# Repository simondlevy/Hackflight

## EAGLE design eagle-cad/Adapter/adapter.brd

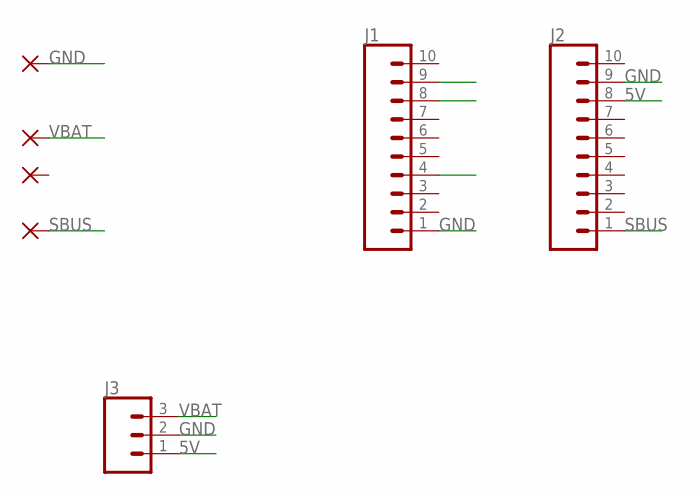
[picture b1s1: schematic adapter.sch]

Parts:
GND: SMD2; SMD1,27-2,54
J1, J2: CONN_10NO_SILK_PTH_FEMALE; 1X10_NO_SILK
J3: CONN_031X03_NO_SILK; 1X03_NO_SILK
PAD1: SMD2; SMD1,27-2,54
SBUS: SMD2; SMD1,27-2,54
VBAT: SMD2; SMD1,27-2,54

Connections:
3V3: J1.4
5V: J2.8, J3.1
GND: GND.1, J1.1, J2.9, J3.2
M2: J1.9
M3: J1.8
SBUS: J2.1, SBUS.1
VBAT: J3.3, VBAT.1

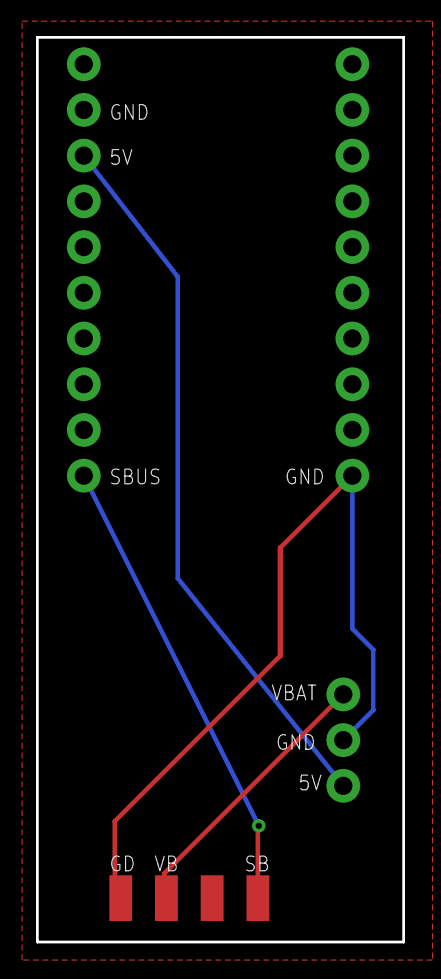
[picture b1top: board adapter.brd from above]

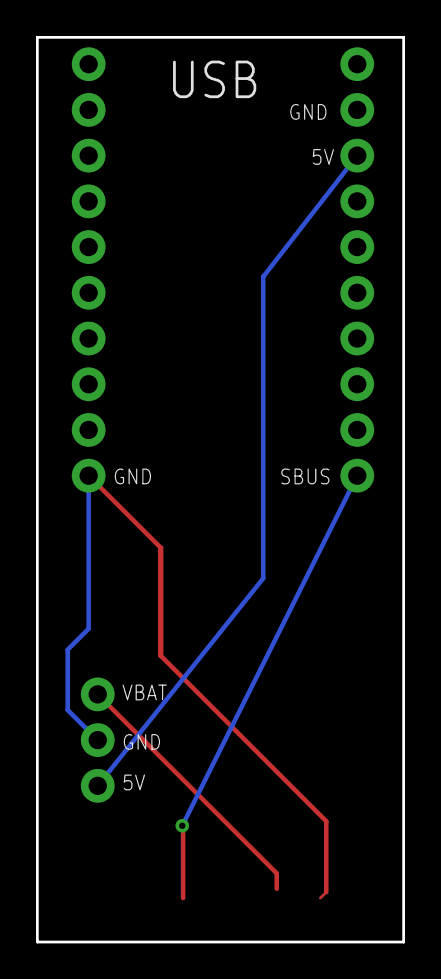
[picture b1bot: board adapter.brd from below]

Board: 2 copper layers, 20.4 x 50.3 mm, 7 parts (2 on the bottom side), 4 nets.

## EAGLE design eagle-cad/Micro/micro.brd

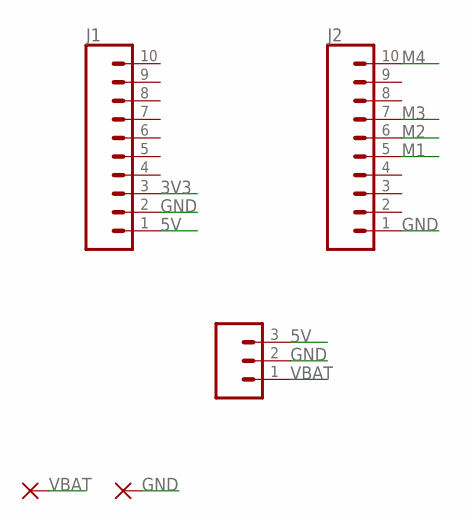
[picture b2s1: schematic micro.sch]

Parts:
J1, J2: CONN_10NO_SILK_PTH_FEMALE; 1X10_NO_SILK
J3: CONN_031X03_NO_SILK; 1X03_NO_SILK
PAD1, PAD2: SMD5; SMD2,54-5,08

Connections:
3V3: J1.3
5V: J1.1, J3.3
GND: J1.2, J2.1, J3.2, PAD2.1
M1: J2.5
M2: J2.6
M3: J2.7
M4: J2.10
VBAT: J3.1, PAD1.1

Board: 2 copper layers, 5 parts (0 on the bottom side), 3 nets, no tracks yet.

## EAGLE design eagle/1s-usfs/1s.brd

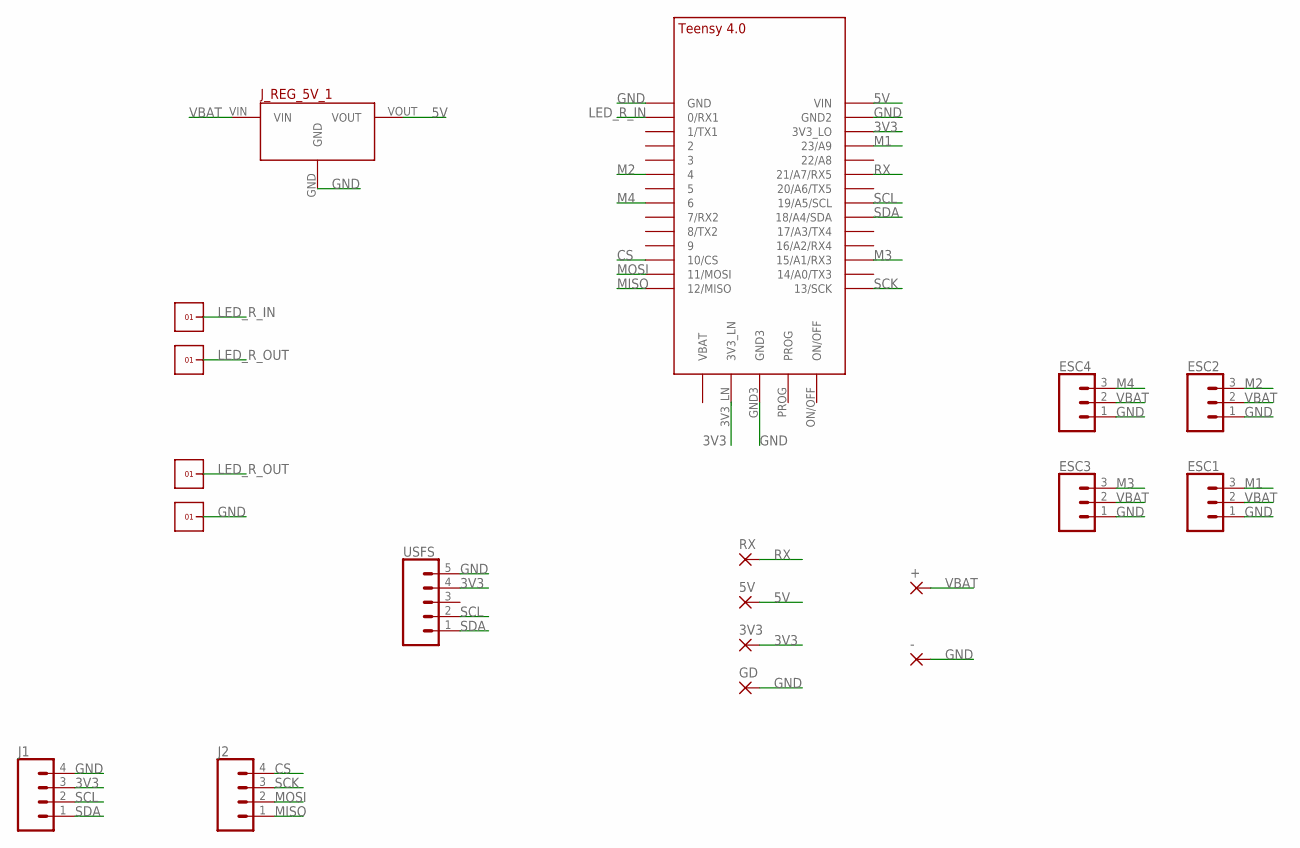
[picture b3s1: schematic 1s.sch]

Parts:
3V3, 5V: SMD2; SMD1,27-2,54
+: SMD5; SMD2,54-5,08
-: SMD5; SMD2,54-5,08
ESC1, ESC2, ESC3, ESC4: 455-1750-1-ND; 1X03
GD: SMD2; SMD1,27-2,54
J1, J2: CONN_041X04_NO_SILK; 1X04_NO_SILK
J_REG_5V_1: 5V_VOLTAGE_REGULATOR
RX: SMD2; SMD1,27-2,54
U$1: TEENSY_4.0
U$3, U$4, U$6, U$7: 1X1
USFS: CONN_05NO_SILK; 1X05_NO_SILK

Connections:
3V3: 3V3.1, J1.3, U$1.3V3_LN, U$1.3V3_LO, USFS.4
5V: 5V.1, J_REG_5V_1.VOUT, U$1.VIN
CS: J2.4, U$1.10/CS
GND: -.1, ESC1.1, ESC2.1, ESC3.1, ESC4.1, GD.1, J1.4, J_REG_5V_1.GND, U$1.GND, U$1.GND2, U$1.GND3, U$7.1, USFS.5
LED_R_IN: U$1.0/RX (0/RX1), U$3.1
LED_R_OUT: U$4.1, U$6.1
M1: ESC1.3, U$1.23/A9
M2: ESC2.3, U$1.4/CANRX (4)
M3: ESC3.3, U$1.15/A1 (15/A1/RX3)
M4: ESC4.3, U$1.6
MISO: J2.1, U$1.12/MISO
MOSI: J2.2, U$1.11/MOSI
RX: RX.1, U$1.21/A7 (21/A7/RX5)
SCK: J2.3, U$1.13/SCK
SCL: J1.2, U$1.19/A5/SCL, USFS.2
SDA: J1.1, U$1.18/A4/SDA, USFS.1
VBAT: +.1, ESC1.2, ESC2.2, ESC3.2, ESC4.2, J_REG_5V_1.VIN

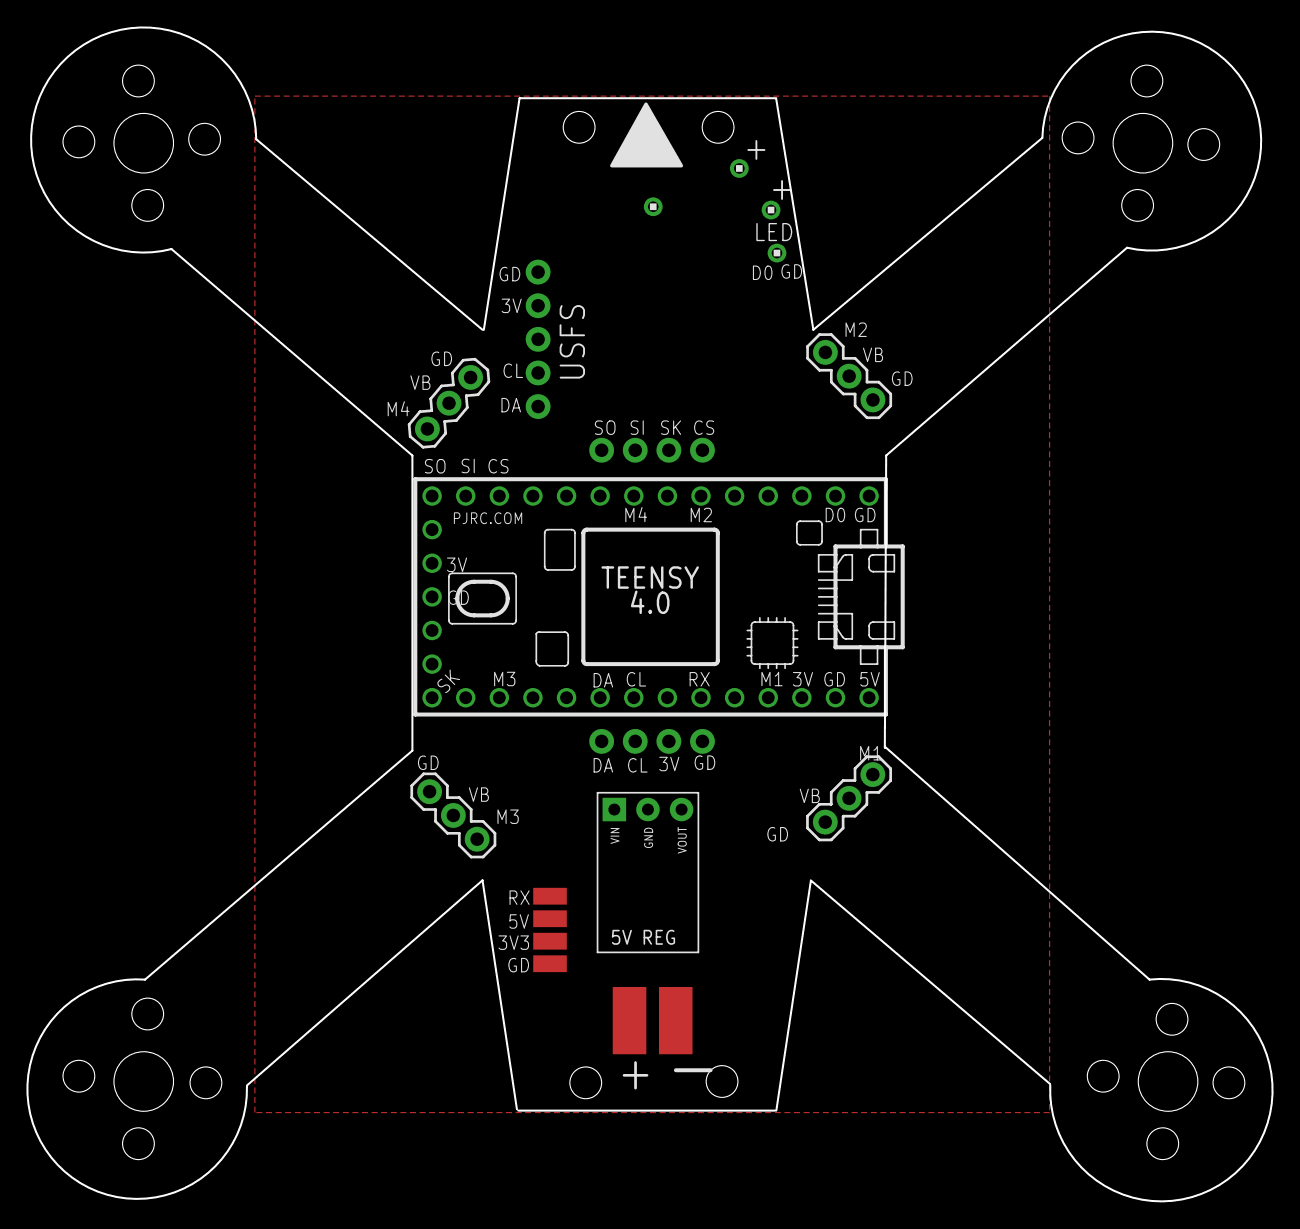
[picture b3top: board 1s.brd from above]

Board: 2 copper layers, 94.1 x 88.7 mm, 19 parts (0 on the bottom side), 17 nets.

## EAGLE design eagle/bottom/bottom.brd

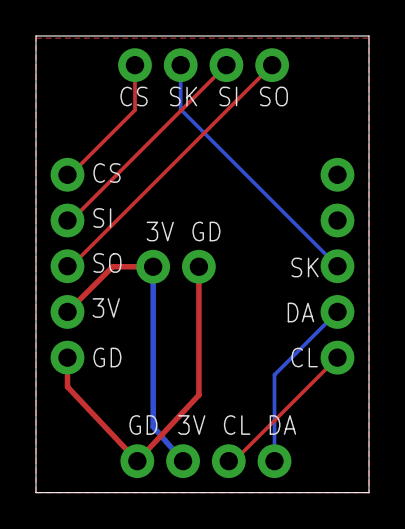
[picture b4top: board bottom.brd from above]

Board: 2 copper layers, 18.5 x 25.4 mm, 5 parts (0 on the bottom side), 8 nets.

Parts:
J3, J5: 1X04_NO_SILK
J4: 1X02_NO_SILK
J6, J7: 1X05_NO_SILK

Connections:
3V3: J3.3, J4.2, J6.2
CS: J5.1, J6.5
GND: J3.4, J4.1, J6.1
MISO: J5.4, J6.3
MOSI: J5.3, J6.4
SCK: J5.2, J7.3
SCL: J3.2, J7.1
SDA: J3.1, J7.2

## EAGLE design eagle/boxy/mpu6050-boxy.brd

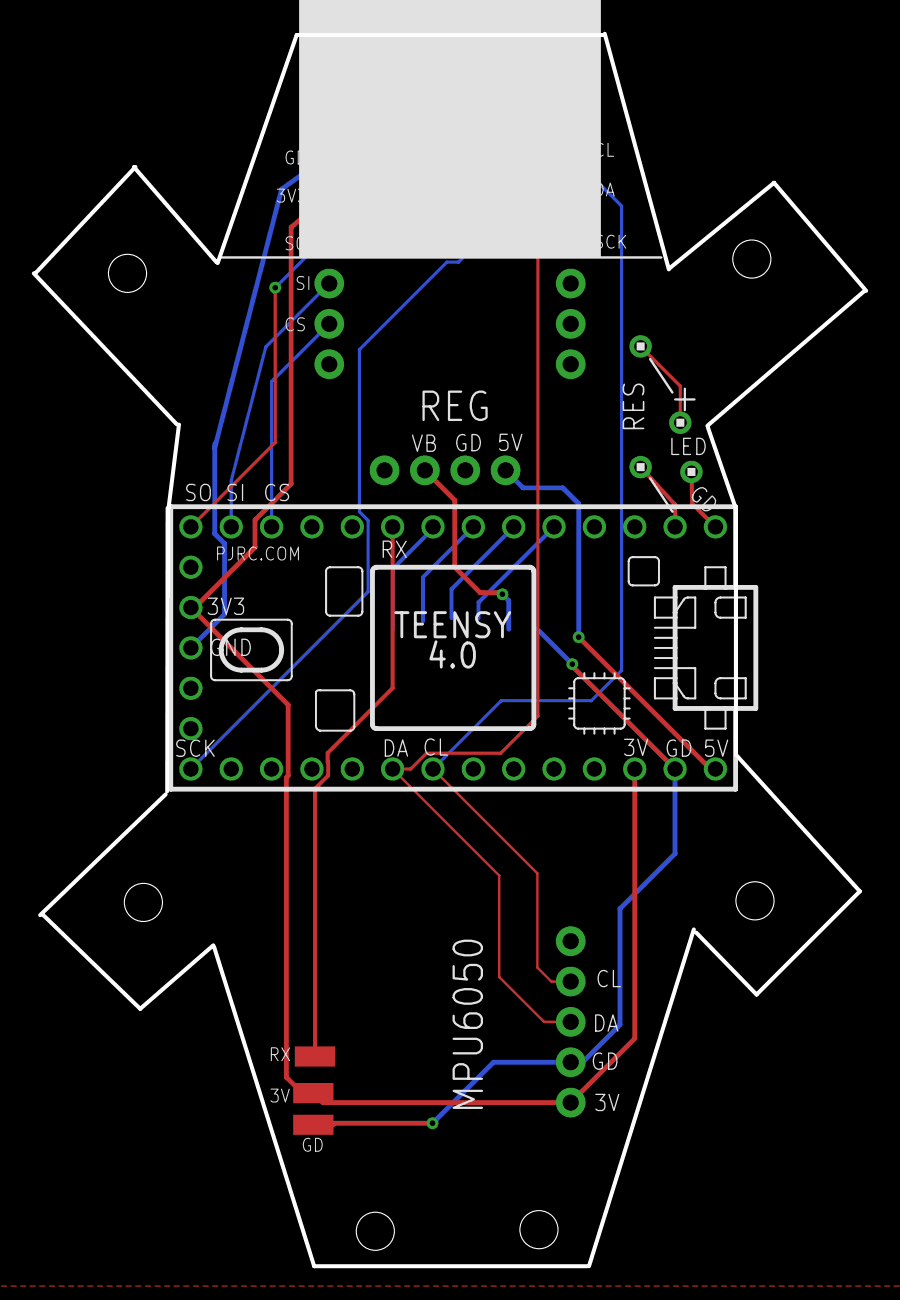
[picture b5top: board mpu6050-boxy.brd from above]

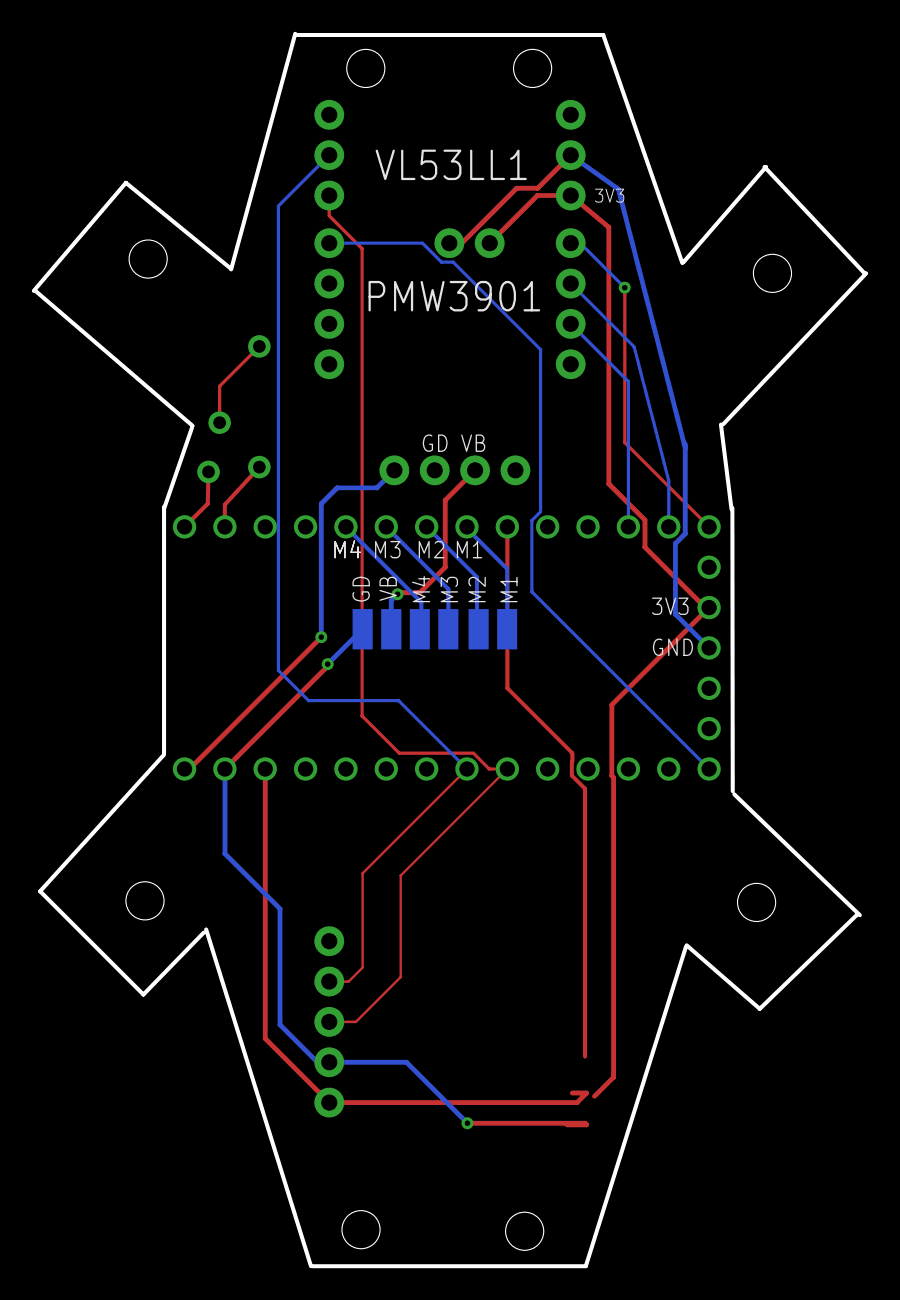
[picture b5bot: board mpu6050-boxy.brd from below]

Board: 2 copper layers, 52.4 x 77.6 mm, 21 parts (6 on the bottom side), 18 nets.

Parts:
3V: SMD1,27-2,54
GD: SMD1,27-2,54
GND: SMD1,27-2,54
J1: 1X05_NO_SILK
M1, M2, M3, M4: SMD1,27-2,54
PMW1, PMW2: 1X04_NO_SILK
PMW3: 1X02_NO_SILK
REG: 1X04_NO_SILK
RX: SMD1,27-2,54
U$1: TEENSY_4.0
U$3, U$4, U$6, U$7: 1X1
VBAT: SMD1,27-2,54
VL1, VL2: 1X03_NO_SILK

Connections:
3V3: 3V.1, J1.1, PMW3.1, U$1.3V3_LN, U$1.3V3_LO, VL2.1
5V: REG.1, U$1.VIN
CS: PMW2.3, U$1.10/CS
G2: U$1.GND, U$7.1
GND: GD.1, GND.1, J1.2, PMW3.2, REG.2, U$1.GND2, U$1.GND3, VL2.2
LED_R_IN: U$1.0/RX, U$3.1
LED_R_OUT: U$4.1, U$6.1
M1: M1.1, U$1.6
M2: M2.1, U$1.5
M3: M3.1, U$1.4/CANRX
M4: M4.1, U$1.3/CANTX
MISO: PMW2.1, U$1.12/MISO
MOSI: PMW2.2, U$1.11/MOSI
RX: RX.1, U$1.7
SCK: PMW1.1, U$1.13/SCK
SCL: J1.4, U$1.19/A5/SCL, VL1.2
SDA: J1.3, U$1.18/A4/SDA, VL1.1
VBAT: REG.3, VBAT.1

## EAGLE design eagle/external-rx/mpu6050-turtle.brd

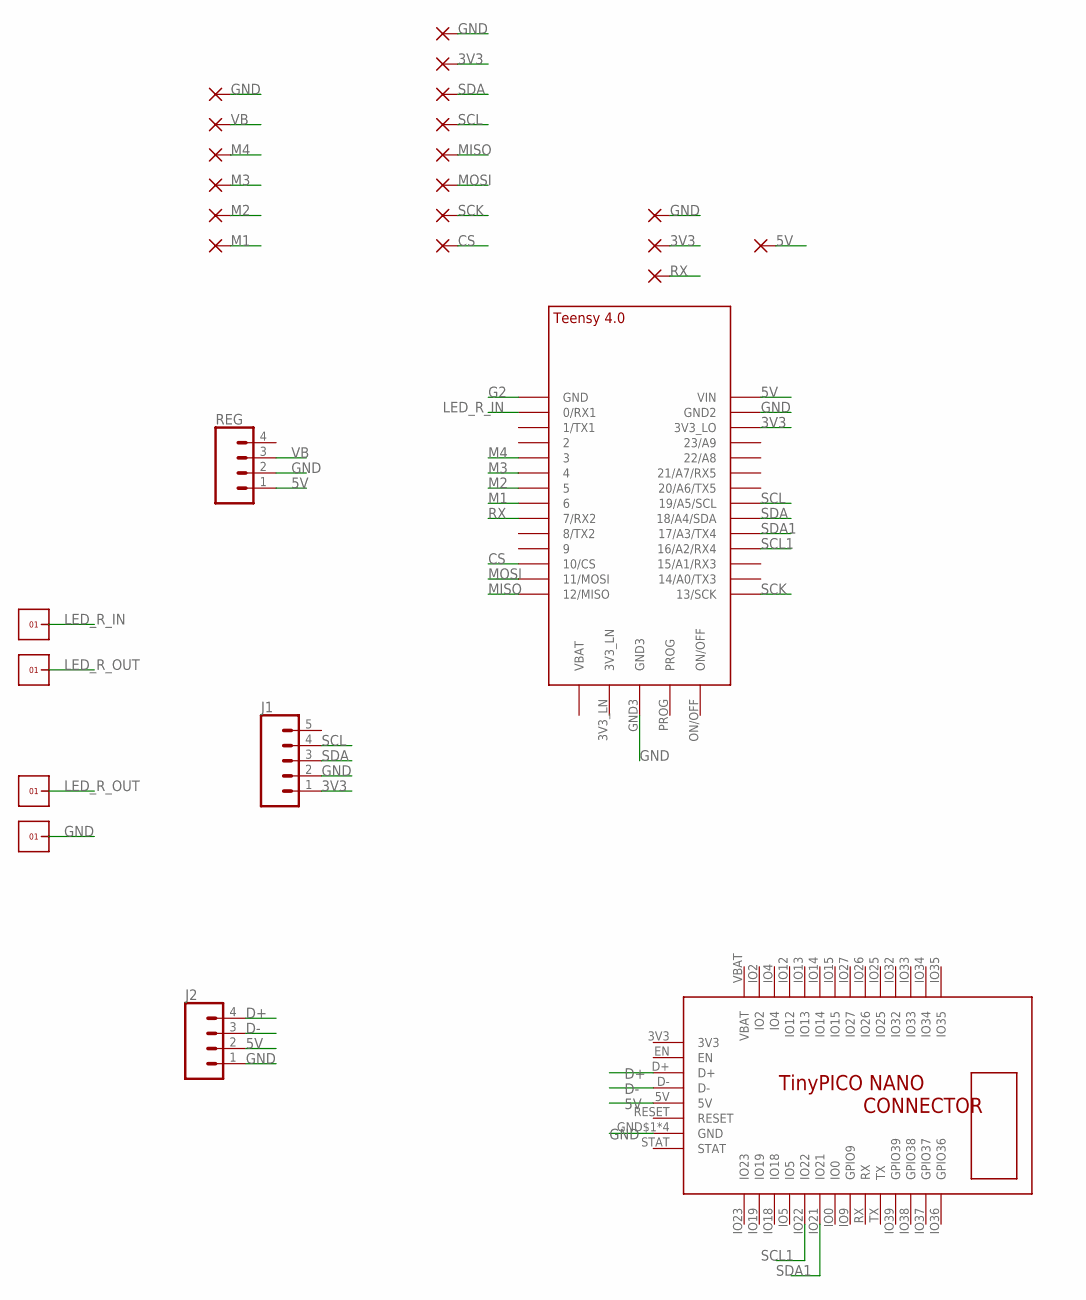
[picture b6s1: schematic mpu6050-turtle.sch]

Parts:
3V, 3V1, 3V2, 3V3: SMD2; SMD1,27-2,54
CS: SMD2; SMD1,27-2,54
GD, GD1, GD2: SMD2; SMD1,27-2,54
GND: SMD2; SMD1,27-2,54
J1: CONN_05NO_SILK; 1X05_NO_SILK
J2: CONN_041X04_NO_SILK; 1X04_NO_SILK
M1, M2, M3, M4: SMD2; SMD1,27-2,54
REG: CONN_041X04_NO_SILK; 1X04_NO_SILK
RX, RX1, RX2: SMD2; SMD1,27-2,54
SCK: SMD2; SMD1,27-2,54
U$1: TEENSY_4.0
U$2: TINYPICO-NANO-CONNECTOR
U$3, U$4, U$6, U$7: 1X1
VBAT: SMD2; SMD1,27-2,54

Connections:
3V3: 3V.1, 3V2.1, J1.1, U$1.3V3_LO, U$2.3V3
5V: 3V1.1, J2.2, REG.1, U$1.VIN, U$2.5V
CS: CS.1, U$1.10/CS
D+: J2.4, U$2.D+
D-: J2.3, U$2.D-
G2: U$1.GND
GND: GD.1, GD1.1, GND.1, J1.2, J2.1, REG.2, U$1.GND2, U$1.GND3, U$2.GND$1 (GND), U$2.GND$2 (GND), U$2.GND$3 (GND), U$2.GND$4 (GND), U$7.1
LED_R_IN: U$1.0/RX (0/RX1), U$3.1
LED_R_OUT: U$4.1, U$6.1
M1: M1.1, U$1.6
M2: M2.1, U$1.5
M3: M3.1, U$1.4/CANRX (4)
M4: M4.1, U$1.3/CANTX (3)
MISO: 3V3.1, U$1.12/MISO
MOSI: RX2.1, U$1.11/MOSI
RX: RX.1, U$1.7 (7/RX2)
SCK: SCK.1, U$1.13/SCK
SCL: GD2.1, J1.4, U$1.19/A5/SCL
SCL1: U$1.16/A2 (16/A2/RX4), U$2.IO22
SDA: J1.3, RX1.1, U$1.18/A4/SDA
SDA1: U$1.17/A3 (17/A3/TX4), U$2.IO21
VB: REG.3, U$2.VBAT, VBAT.1

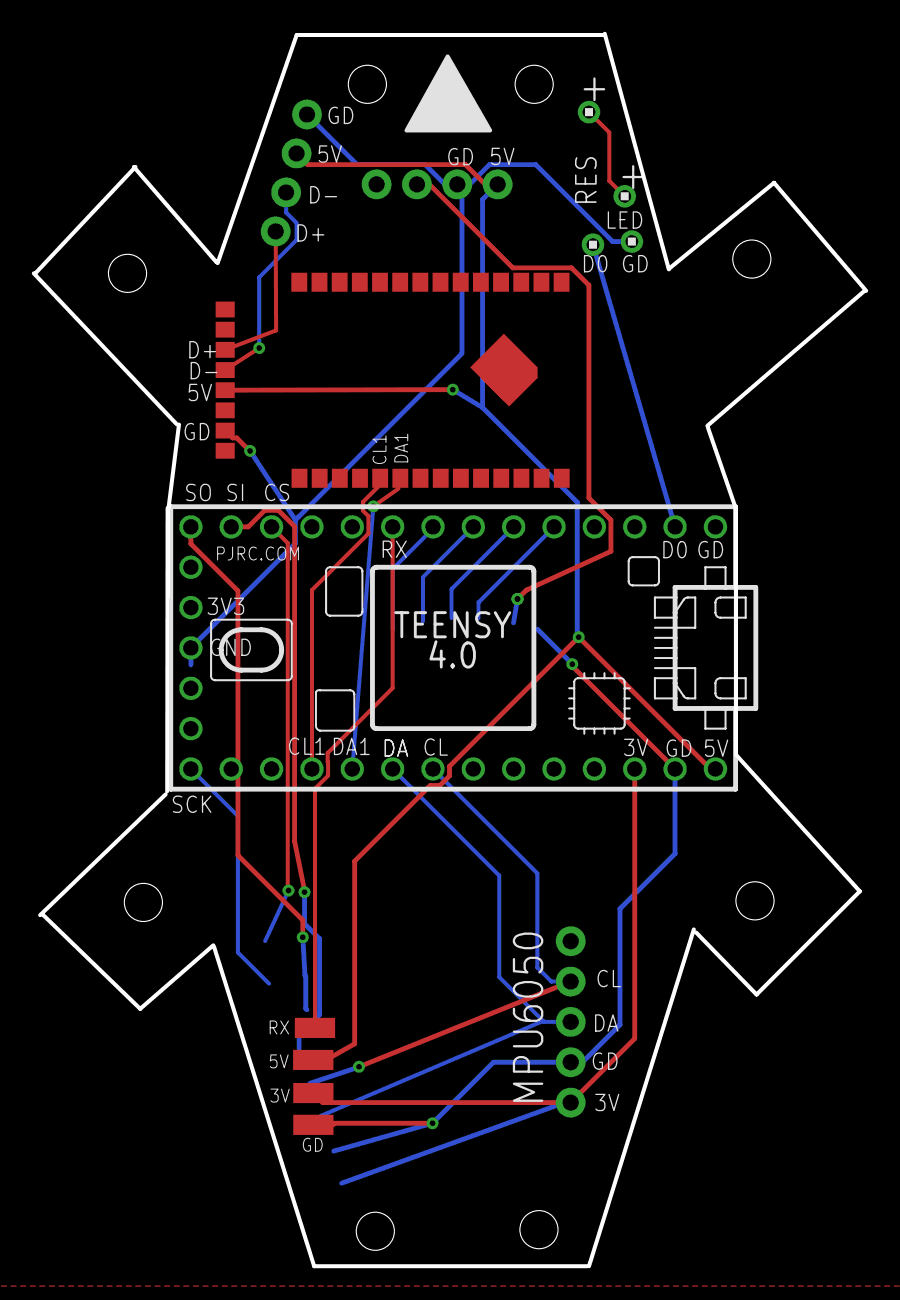
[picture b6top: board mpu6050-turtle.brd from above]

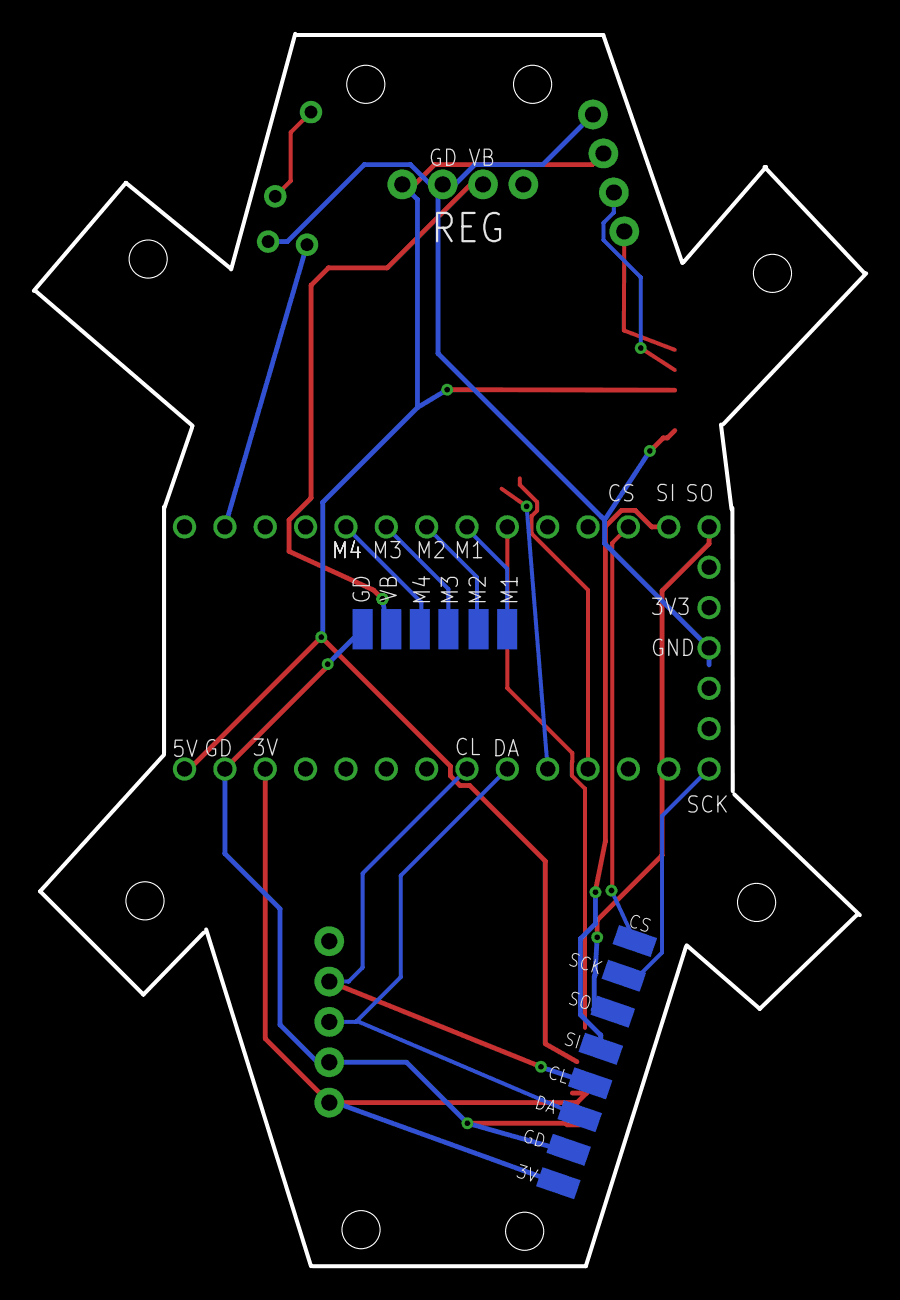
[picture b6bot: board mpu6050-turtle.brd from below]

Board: 2 copper layers, 52.4 x 77.6 mm, 27 parts (14 on the bottom side), 21 nets.

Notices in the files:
parts and their libraries:
SparkFun-Connectors: Licensing: Creative Commons ShareAlike 4.0 International - https://creativecommons.org/licenses/by-sa/4.0
